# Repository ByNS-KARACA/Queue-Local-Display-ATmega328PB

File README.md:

# Queue Local Display – ATmega328PB

A modular local queue display controller designed for queue management systems used in hospitals, banks, clinics, public institutions, service counters, and similar environments.

The system is built around the **Microchip ATmega328PB** microcontroller and supports both wired **RS-485 communication** and optional **433 MHz HC-12 wireless communication**.

The display section uses cascaded **HEF4094BT shift registers**, allowing multiple large 7-segment displays to be controlled with only a few MCU pins.

## Features

* Microchip **ATmega328PB**
* 5 V MCU operation
* External **16 MHz crystal**
* 12 V DC input
* **AP63205WU-7** synchronous buck converter for 12 V to 5 V
* **MAX485** RS-485 interface
* Optional **HC-12 433 MHz wireless module**
* Independent hardware UARTs for RS-485 and HC-12
* **HEF4094BT** cascaded display architecture
* **ULN2003A** 5 V to 12 V logic interface
* Static-drive 7-segment display architecture
* 6 × large 56 mm 7-segment display positions
* 2 display positions support optional FJ11001AH alternative displays
* EEPROM-based device addressing
* SET / UP / DOWN configuration buttons
* PWM-capable global display brightness control
* External I²C expansion interface
* Additional GPIO expansion pins
* RS-485 daisy-chain capability
* Optional RS-485 termination
* Designed for continuous **24/7 operation**

## 3D Preview

### Top & Bottom Views

### Angled View

## Manufacturing Files

Ready-to-manufacture Gerber and drill files are provided for this PCB.

- 📁 [Browse Gerber Files](Hardware/Gerber)
- 📦 [Download Complete Gerber ZIP](Hardware/Gerber/Queue_Local_Display_Atmega328PB_GERBER.zip)
- 🛠️ [KiCad Source Files](Hardware/KiCad)
- 📋 [Bill of Materials (BOM)](Hardware/BOM/Queue_Local_Display_ATmega328PB_BOM.xlsx)
The Gerber package includes the copper, solder mask, silkscreen, solder paste, board outline, plated-hole and non-plated-hole drill files required for PCB fabrication.

### PCB Specifications

| Parameter | Specification |
| --- | --- |
| Layers | 2 |
| PCB Thickness | 1.6 mm |
| Material | FR-4 |
| Copper Thickness | 35 µm / 1 oz |
| Board Size | approximately 340.05 × 100.05 mm |

> **Note:** Always verify the Gerber files and manufacturing parameters with your PCB manufacturer before placing an order.

## Display Configuration

The board uses:

### Main Queue Number

* 4 × **SM412301N**
* 2.3 inch / approximately 56 mm
* Red
* Common Anode
### Optional Alternative Display

Two display positions also support:

- 2 × **FJ11001AH**
- Smaller red 7-segment display
- Optional alternative to SM412301N
- Not populated simultaneously with SM412301N at the same position
### Counter / Desk Number

* 2 × **FJ11001AH**
* Red 7-segment display

Example display format:

```text
+--------------------------------+
|                                |
|       A 1 4 5       0 3        |
|                                |
|       QUEUE        COUNTER      |
+--------------------------------+
```

## Display Driver Architecture

Each 7-segment digit is controlled by its own **HEF4094BT** shift register.

The shift registers are connected in cascade:

```text
ATmega328PB
     |
     | DATA
     v
 HEF4094 #1
     |
    QS2
     v
 HEF4094 #2
     |
    QS2
     v
 HEF4094 #3
     |
    QS2
     v
 HEF4094 #4
     |
    QS2
     v
 HEF4094 #5
     |
    QS2
     v
 HEF4094 #6
```

CLOCK, STROBE and OE lines are shared between all HEF4094 devices.

The HEF4094 devices operate from the **12 V rail**.

A **ULN2003A open-collector interface** with 12 V pull-up resistors is used between the 5 V ATmega328PB and the 12 V HEF4094 control inputs.

## HEF4094 Control Pins

| Function | ATmega328PB |
| -------- | ----------- |
| DATA     | D4          |
| OE       | D5          |
| CLOCK    | D6          |
| STROBE   | D7          |

The OE line is connected to a PWM-capable MCU output, allowing global display brightness control.

## RS-485 Interface

The board uses a **MAX485** half-duplex RS-485 transceiver.

| Function  | ATmega328PB |
| --------- | ----------- |
| RS-485 RX | PD0 / RXD0  |
| RS-485 TX | PD1 / TXD0  |
| RE + DE   | PB0 / D8    |

The RE and DE pins are connected together and controlled from a single GPIO.

The board is designed for **RS-485 bus / daisy-chain wiring**.

```text
MASTER
   |
LOCAL DISPLAY 01
   |
LOCAL DISPLAY 02
   |
LOCAL DISPLAY 03
   |
LOCAL DISPLAY 04
```

A termination resistor footprint is provided for installations where the display is located at the physical end of the RS-485 bus.

## HC-12 Wireless Interface

An optional **HC-12 433 MHz UART module** can be installed.

ATmega328PB USART1 is used for wireless communication.

| Function  | ATmega328PB |
| --------- | ----------- |
| HC-12 RX  | PB3 / TXD1  |
| HC-12 TX  | PB4 / RXD1  |
| HC-12 SET | PB2 / D10   |

The SET input includes a pull-up resistor to keep the HC-12 in normal operating mode during startup.

## Device Address Configuration

Each local display can be assigned an individual device address.

Three buttons are used:

* **SET**
* **UP**
* **DOWN**

The selected address is stored in the internal EEPROM of the ATmega328PB.

This eliminates the need for DIP switches and simplifies installation and field configuration.

## Power Architecture

```text
12 V DC INPUT
      |
      +--------------------> Displays / HEF4094 / LEDs
      |
      +----> AP63205WU-7
                  |
                  v
                 5 V
                  |
                  +----> ATmega328PB
                  +----> MAX485
                  +----> HC-12
```

The **AP63205WU-7** provides the regulated 5 V logic supply.

The 12 V rail directly supplies the display driver section and external indicators.

## Expansion

Unused ATmega328PB GPIO pins are exposed for future expansion.

Possible future uses include:

* Status LEDs
* Additional buttons
* External sensors
* Relay outputs
* ADC inputs
* Interrupt inputs
* Additional I²C devices
* External indicators

The primary external I²C interface is:

```text
PC4 → SDA0
PC5 → SCL0
```

## Applications

* Hospital queue systems
* Bank queue systems
* Clinic waiting-room displays
* Government service counters
* Pharmacy queue systems
* Restaurant queue systems
* Reception systems
* Service desk displays

## Modular Architecture

The hardware is designed with future modular expansion in mind.

Multiple local display boards can later be combined to create a multi-row **main queue display**, while maintaining a common hardware platform.

## Project Status

**Hardware Design:** Completed
**Firmware:** In Development
**Production Validation:** Pending

This project is currently in the prototype and validation stage.

## Disclaimer

This hardware should be fully tested and validated before use in commercial, medical, industrial, or safety-critical installations.

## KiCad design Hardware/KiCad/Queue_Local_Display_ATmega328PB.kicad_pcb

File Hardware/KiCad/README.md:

# KiCad Design Files

This directory contains the KiCad source files for the Queue Local Display hardware.

## Files

- Schematic design
- PCB layout
- KiCad project file

These files represent the editable hardware source of the project.

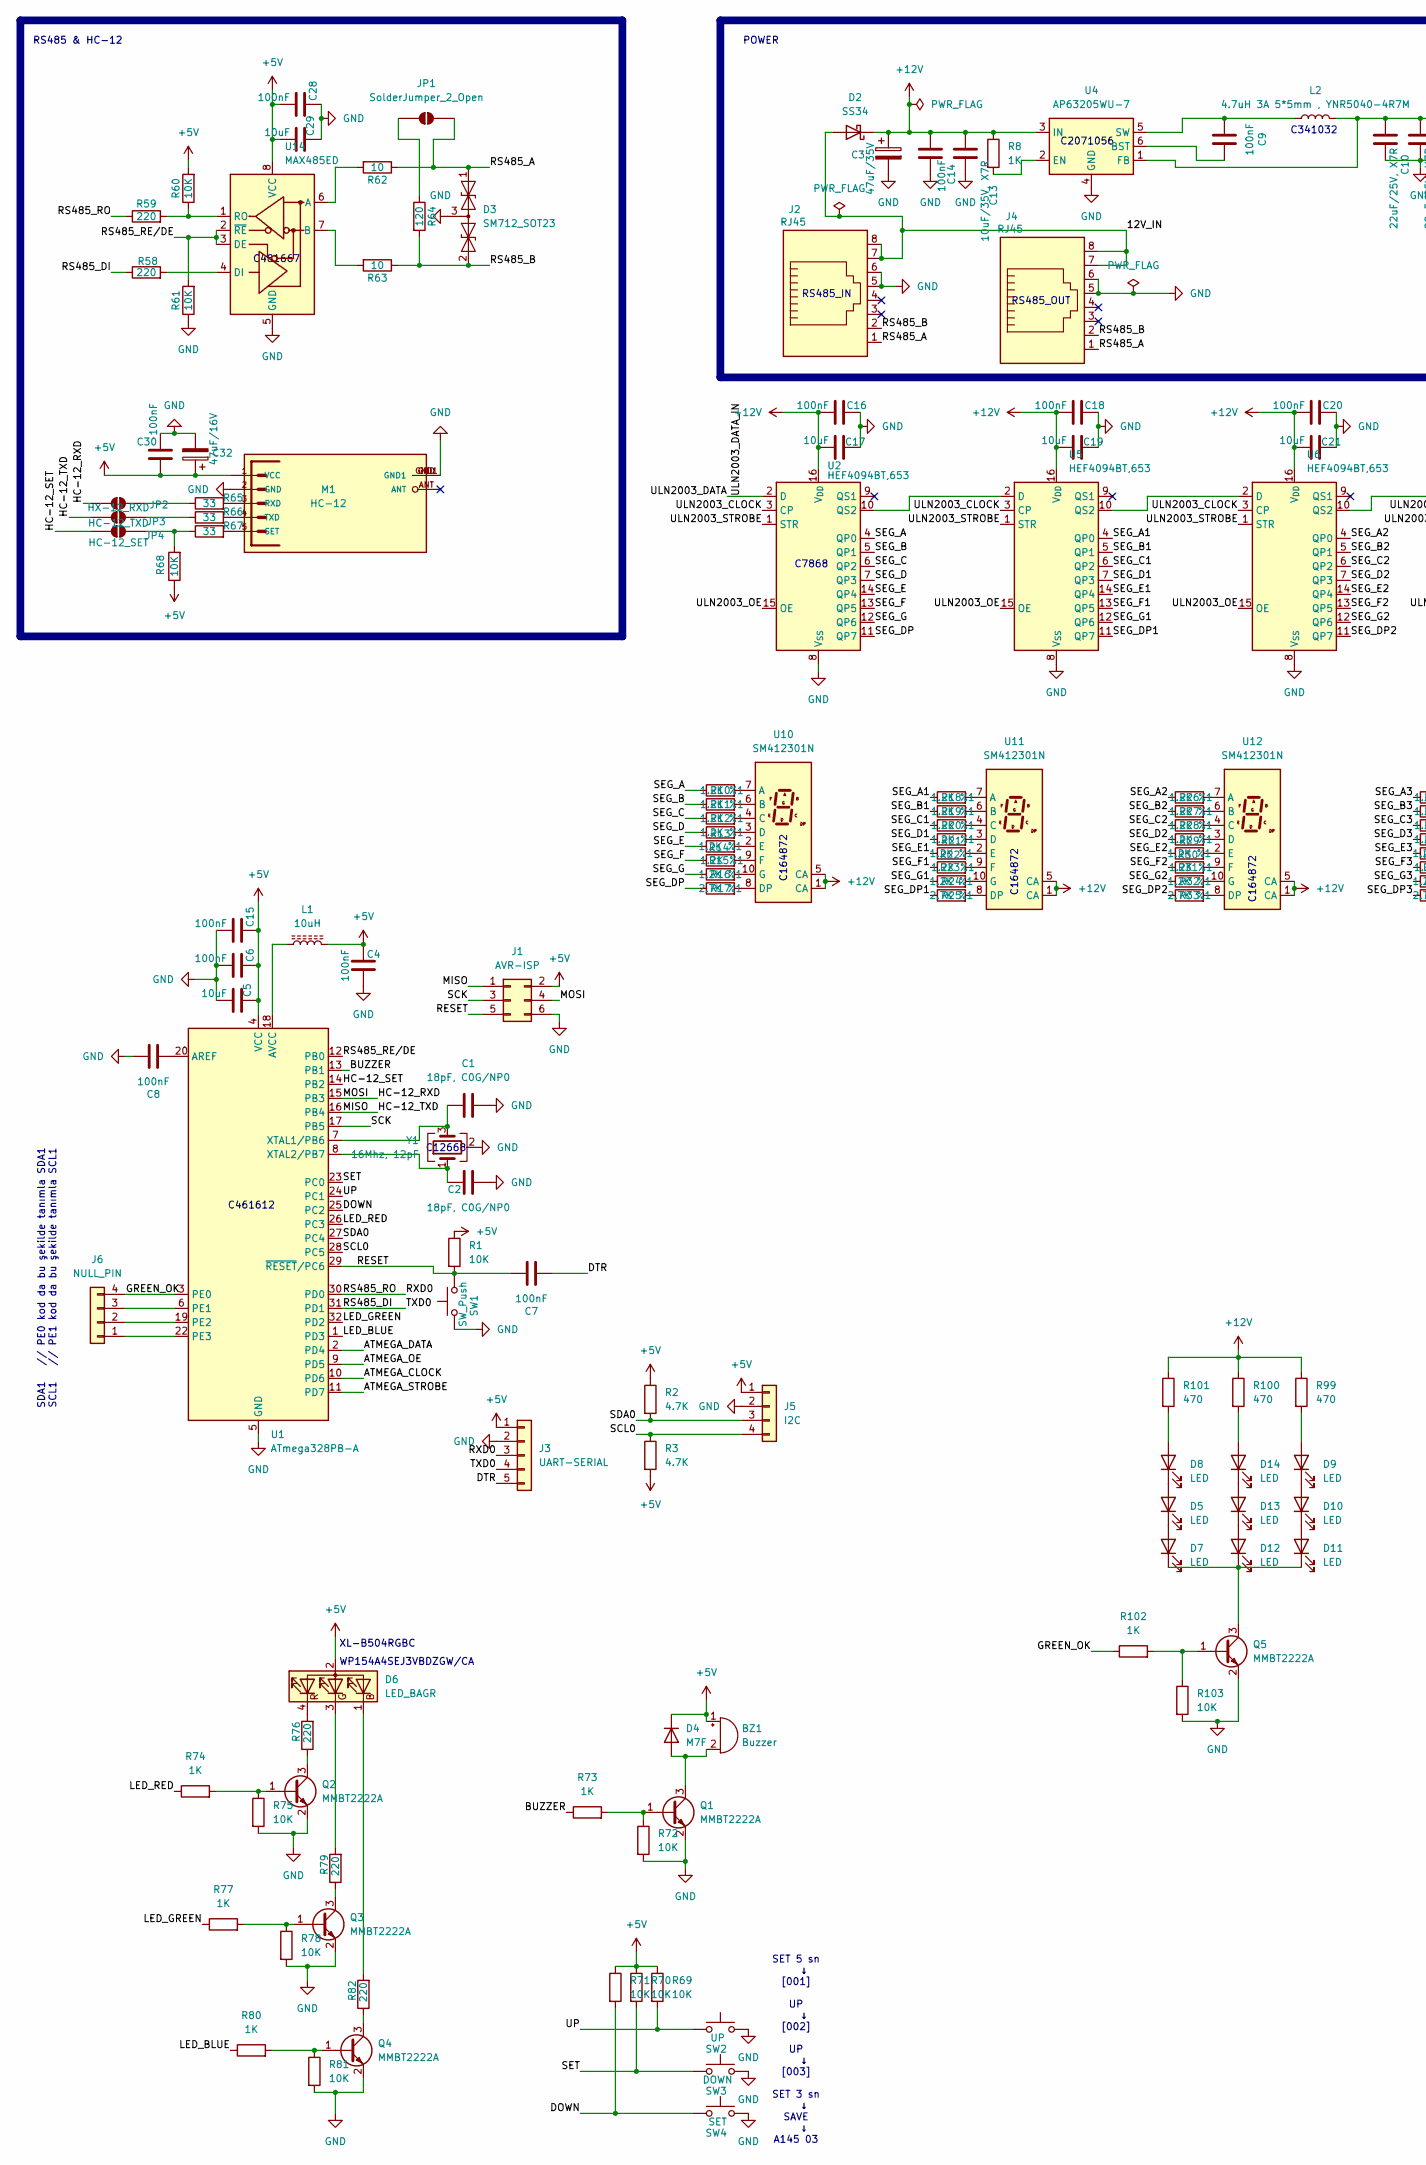
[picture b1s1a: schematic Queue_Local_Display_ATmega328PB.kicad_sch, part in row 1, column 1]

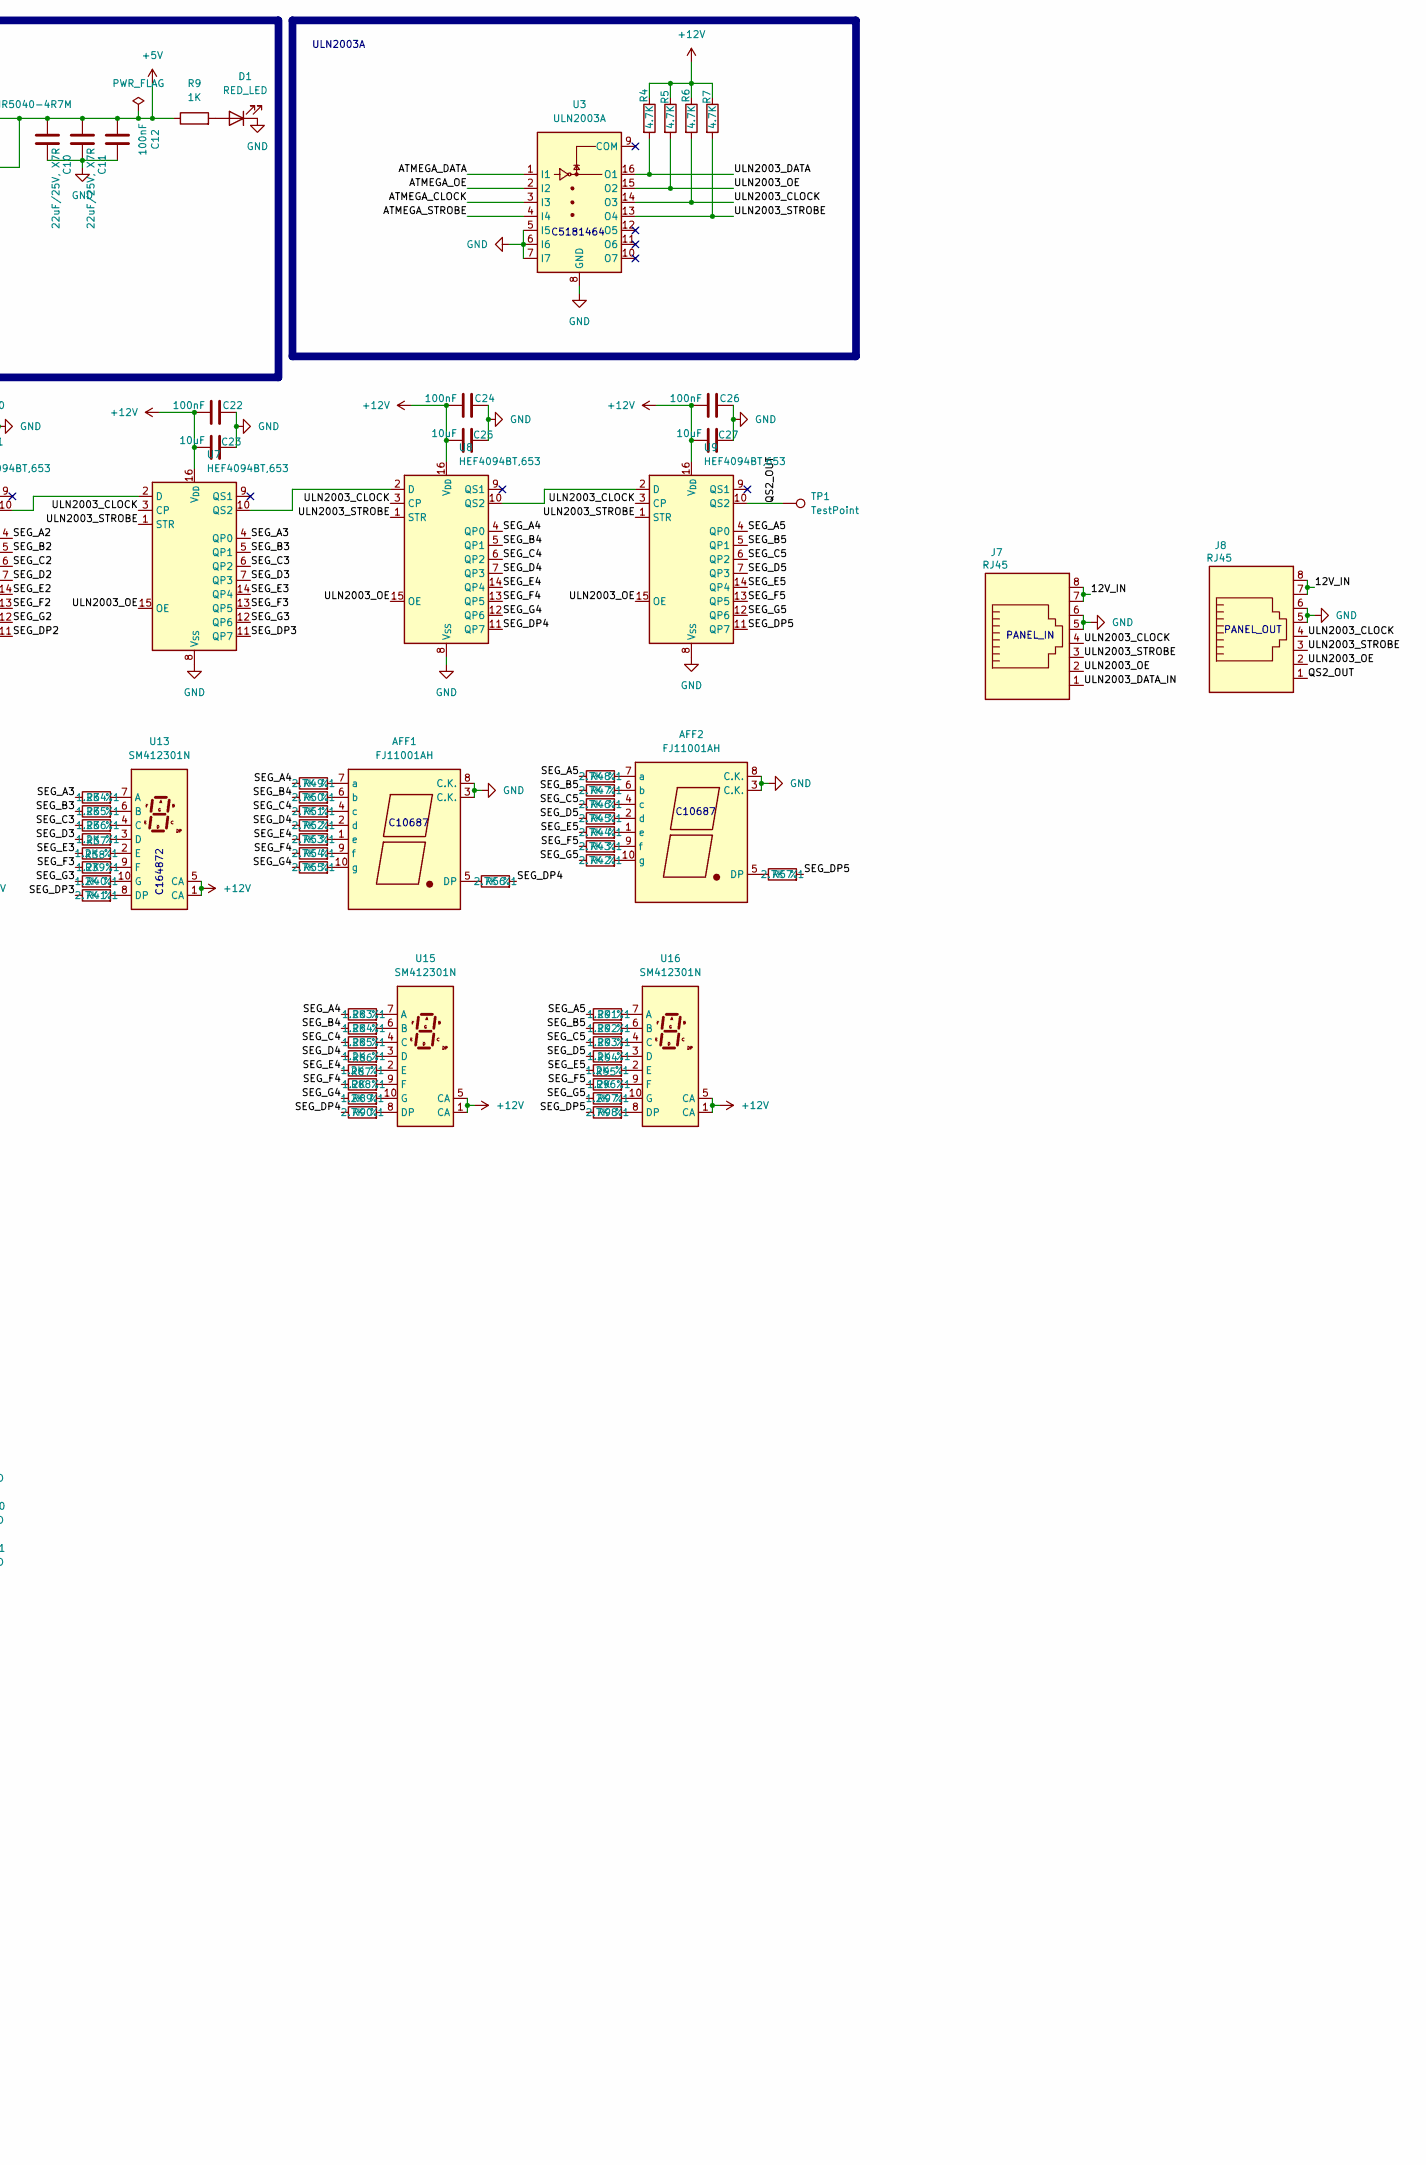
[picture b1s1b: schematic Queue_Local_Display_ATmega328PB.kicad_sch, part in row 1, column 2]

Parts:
AFF1, AFF2: FJ11001AH; 7SegmentLED_LTS6760_LTS6780
BZ1: Buzzer; Buzzer_12x9.5RM7.6
C1, C2: 18pF, C0G/NP0; C_0603_1608Metric
C3: 47uF/35V; CP_Elec_6.3x5.4
C4, C6, C8, C15, C16, C18, C20, C22, C24, C26, C28, C30: 100nF; C_0603_1608Metric
C5, C17, C19, C21, C23, C25, C27, C29: 10uF; C_0805_2012Metric
C7, C9, C12, C14: 100nF; C_0805_2012Metric
C10, C11: 22uF/25V, X7R; C_1206_3216Metric
C13: 10uF/35V, X7R; C_1206_3216Metric
C32: 47uF/16V; CP_Elec_5x5.7
D1: RED_LED; LED_0805_2012Metric
D2: SS34; D_SMA
D3: SM712_SOT23; SOT-23
D4: M7F; D_SMA
D5, D7, D8, D9, D10, D11, D12, D13, D14: LED; LED_1206_3216Metric
D6: LED_BAGR; LED_D5.0mm-4_RGB_Wide_Pins
J1: AVR-ISP; PinHeader_2x03_P2.54mm_Vertical
J2, J4, J7, J8: RJ45; RJ45_Amphenol_54602-x08_Horizontal
J3: UART-SERIAL; PinHeader_1x05_P2.54mm_Vertical
J5: I2C; PinHeader_1x04_P2.54mm_Vertical
J6: NULL_PIN; PinHeader_1x04_P2.54mm_Vertical
JP1: SolderJumper_2_Open; SolderJumper-2_P1.3mm_Open_RoundedPad1.0x1.5mm
JP2: HX-12_RXD; SolderJumper-2_P1.3mm_Open_RoundedPad1.0x1.5mm
JP3: HC-12_TXD; SolderJumper-2_P1.3mm_Open_RoundedPad1.0x1.5mm
JP4: HC-12_SET; SolderJumper-2_P1.3mm_Open_RoundedPad1.0x1.5mm
L1: 10uH; L_0603_1608Metric
L2: 4.7uH 3A 5*5mm , YNR5040-4R7M; L_Chilisin_BWVS00505040
M1: HC-12; MA05-1
Q1, Q2, Q3, Q4, Q5: MMBT2222A; SOT-23
R1, R60, R61, R68: 10K; R_0805_2012Metric
R2, R3, R4, R5, R6, R7: 4.7K; R_0805_2012Metric
R8, R9: 1K; R_0805_2012Metric
R10, R11, R12, R13, R14, R15, R16, R18, R19, R20, R21, R22, R23, R24, R26, R27, R28, R29, R30, R31, R32, R34, R35, R36, R37, R38, R39, R40, R83, R84, R85, R86, R87, R88, R89, R91, R92, R93, R94, R95, R96, R97: 1.2K %1; R_0805_2012Metric
R17, R25, R33, R41, R42, R43, R44, R45, R46, R47, R48, R49, R50, R51, R52, R53, R54, R55, R56, R57, R90, R98: 2.7K %1; R_0805_2012Metric
R58, R59: 220; R_0805_2012Metric
R62, R63: 10; R_0805_2012Metric
R64: 120; R_0805_2012Metric
R65, R66, R67: 33; R_0805_2012Metric
R69, R70, R71, R72, R75, R78, R81, R103: 10K; R_0603_1608Metric
R73, R74, R77, R80, R102: 1K; R_0603_1608Metric
R76, R79, R82: 220; R_0603_1608Metric
R99, R100, R101: 470; R_0805_2012Metric
SW1: SW_Push; SW_PUSH_6mm_H13mm
SW2: UP; SW_PUSH_6mm_H13mm
SW3: DOWN; SW_PUSH_6mm_H13mm
SW4: SET; SW_PUSH_6mm_H13mm
TP1: TestPoint; TestPoint_Pad_2.0x2.0mm
U1: ATmega328PB-A; TQFP-32_7x7mm_P0.8mm
U2, U5, U6, U7, U8, U9: HEF4094BT,653; SOIC-16_3.9x9.9mm_P1.27mm
U3: ULN2003A; SOIC-16_3.9x9.9mm_P1.27mm
U4: AP63205WU-7; TSOT-23-6
U10, U11, U12, U13, U15, U16: SM412301N; SA15-11xxx
U14: MAX485ED; SOIC-8_3.9x4.9mm_P1.27mm
Y1: 16Mhz, 12pF; Crystal_SMD_3225-4Pin_3.2x2.5mm

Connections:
+5V: BZ1.1 (+), C4.1, C5.2, C6.2, C10.1, C11.1, C12.1, C15.2, C28.1, C29.1, C30.1, C32.1, D4.1 (K), D6.2 (A), J1.2, J3.1, J5.1, L1.2, L2.2, M1.1 (VCC), R1.1, R2.1, R3.2, R9.1, R60.2, R68.1, R69.1, R70.1, R71.1, U1.4 (VCC), U4.1 (FB), U14.8 (VCC)
+12V: C3.1, C13.1, C14.1, C16.1, C17.1, C18.1, C19.1, C20.1, C21.1, C22.1, C23.1, C24.1, C25.1, C26.1, C27.1, D2.1 (K), R4.1, R5.1, R6.1, R7.1, R8.1, R99.1, R100.1, R101.1, U2.16 (V_{DD}), U4.3 (IN), U5.16 (V_{DD}), U6.16 (V_{DD}), U7.16 (V_{DD}), U8.16 (V_{DD}), U9.16 (V_{DD}), U10.1 (CA), U10.5 (CA), U11.1 (CA), U11.5 (CA), U12.1 (CA), U12.5 (CA), U13.1 (CA), U13.5 (CA), U15.1 (CA), U15.5 (CA), U16.1 (CA), U16.5 (CA)
/12V_IN: D2.2 (A), J2.7, J2.8, J4.7, J4.8, J7.7, J7.8, J8.7, J8.8
/ATMEGA_CLOCK: U1.10 (PD6), U3.3 (I3)
/ATMEGA_DATA: U1.2 (PD4), U3.1 (I1)
/ATMEGA_OE: U1.9 (PD5), U3.2 (I2)
/ATMEGA_STROBE: U1.11 (PD7), U3.4 (I4)
/BUZZER: R73.1, U1.13 (PB1)
/DTR: C7.1, J3.5
/GREEN_OK: J6.4, R102.1, U1.3 (PE0)
/HC-12_RXD: J1.4, JP2.1 (A), U1.15 (PB3)
/HC-12_SET: JP4.1 (A), U1.14 (PB2)
/HC-12_TXD: J1.1, JP3.1 (A), U1.16 (PB4)
/LED_BLUE: R80.1, U1.1 (PD3)
/LED_GREEN: R77.1, U1.32 (PD2)
/LED_RED: R74.1, U1.26 (PC3)
/QS2_OUT: J8.1, TP1.1 (1_1), U9.10 (QS2)
/RESET: C7.2, J1.5, R1.2, SW1.2, U1.29 (~RESET/PC6)
/RS485_A: D3.1 (A1), J2.1, J4.1, JP1.2 (B), R62.1
/RS485_B: D3.2 (A2), J2.2, J4.2, R63.1, R64.2
/RS485_DI: J3.4, R58.1, U1.31 (PD1)
/RS485_RE/DE: R61.2, U1.12 (PB0), U14.2 (~RE), U14.3 (DE)
/RS485_RO: J3.3, R59.1, U1.30 (PD0)
/SCK: J1.3, U1.17 (PB5)
/SCL0: J5.4, R3.1, U1.28 (PC5)
/SDA0: J5.3, R2.2, U1.27 (PC4)
/SEG_A: R10.1, U2.4 (QP0)
/SEG_A1: R18.1, U5.4 (QP0)
/SEG_A2: R26.1, U6.4 (QP0)
/SEG_A3: R34.1, U7.4 (QP0)
/SEG_A4: R49.1, R83.1, U8.4 (QP0)
/SEG_A5: R48.1, R91.1, U9.4 (QP0)
/SEG_B: R11.1, U2.5 (QP1)
/SEG_B1: R19.1, U5.5 (QP1)
/SEG_B2: R27.1, U6.5 (QP1)
/SEG_B3: R35.1, U7.5 (QP1)
/SEG_B4: R50.1, R84.1, U8.5 (QP1)
/SEG_B5: R47.1, R92.1, U9.5 (QP1)
/SEG_C: R12.1, U2.6 (QP2)
/SEG_C1: R20.1, U5.6 (QP2)
/SEG_C2: R28.1, U6.6 (QP2)
/SEG_C3: R36.1, U7.6 (QP2)
/SEG_C4: R51.1, R85.1, U8.6 (QP2)
/SEG_C5: R46.1, R93.1, U9.6 (QP2)
/SEG_D: R13.1, U2.7 (QP3)
/SEG_D1: R21.1, U5.7 (QP3)
/SEG_D2: R29.1, U6.7 (QP3)
/SEG_D3: R37.1, U7.7 (QP3)
/SEG_D4: R52.1, R86.1, U8.7 (QP3)
/SEG_D5: R45.1, R94.1, U9.7 (QP3)
/SEG_DP: R17.1, U2.11 (QP7)
/SEG_DP1: R25.1, U5.11 (QP7)
/SEG_DP2: R33.1, U6.11 (QP7)
/SEG_DP3: R41.1, U7.11 (QP7)
/SEG_DP4: R56.2, R90.1, U8.11 (QP7)
/SEG_DP5: R57.2, R98.1, U9.11 (QP7)
/SEG_E: R14.1, U2.14 (QP4)
/SEG_E1: R22.1, U5.14 (QP4)
/SEG_E2: R30.1, U6.14 (QP4)
/SEG_E3: R38.1, U7.14 (QP4)
/SEG_E4: R53.1, R87.1, U8.14 (QP4)
/SEG_E5: R44.1, R95.1, U9.14 (QP4)
/SEG_F: R15.1, U2.13 (QP5)
/SEG_F1: R23.1, U5.13 (QP5)
/SEG_F2: R31.1, U6.13 (QP5)
/SEG_F3: R39.1, U7.13 (QP5)
/SEG_F4: R54.1, R88.1, U8.13 (QP5)
/SEG_F5: R43.1, R96.1, U9.13 (QP5)
/SEG_G: R16.1, U2.12 (QP6)
/SEG_G1: R24.1, U5.12 (QP6)
/SEG_G2: R32.1, U6.12 (QP6)
/SEG_G3: R40.1, U7.12 (QP6)
/SEG_G4: R55.1, R89.1, U8.12 (QP6)
/SEG_G5: R42.1, R97.1, U9.12 (QP6)
/ULN2003_CLOCK: J7.4, J8.4, R6.2, U2.3 (CP), U3.14 (O3), U5.3 (CP), U6.3 (CP), U7.3 (CP), U8.3 (CP), U9.3 (CP)
/ULN2003_DATA: J7.1, R4.2, U2.2 (D), U3.16 (O1)
/ULN2003_OE: J7.2, J8.2, R5.2, U2.15 (OE), U3.15 (O2), U5.15 (OE), U6.15 (OE), U7.15 (OE), U8.15 (OE), U9.15 (OE)
/ULN2003_STROBE: J7.3, J8.3, R7.2, U2.1 (STR), U3.13 (O4), U5.1 (STR), U6.1 (STR), U7.1 (STR), U8.1 (STR), U9.1 (STR)
/UP: R69.2, SW2.1, U1.24 (PC1)
GND: AFF1.3 (C.K.), AFF1.8 (C.K.), AFF2.3 (C.K.), AFF2.8 (C.K.), C1.2, C2.1, C3.2, C4.2, C5.1, C6.1, C8.2, C10.2, C11.2, C12.2, C13.2, C14.2, C15.1, C16.2, C17.2, C18.2, C19.2, C20.2, C21.2, C22.2, C23.2, C24.2, C25.2, C26.2, C27.2, C28.2, C29.2, C30.2, C32.2, D1.1 (K), D3.3 (common), J1.6, J2.5, J2.6, J3.2, J4.5, J4.6, J5.2, J7.5, J7.6, J8.5, J8.6, M1.2 (GND), M1.GND (GND1), M1.GND1, Q1.2 (E), Q2.2 (E), Q3.2 (E), Q4.2 (E), Q5.2 (E), R61.1, R72.2, R75.2, R78.2, R81.2, R103.2, SW1.1, SW2.2, SW3.2, SW4.2, U1.5 (GND), U1.21 (GND), U2.8 (V_{SS}), U3.5 (I5), U3.6 (I6), U3.7 (I7), U3.8 (GND), U4.4 (GND), U5.8 (V_{SS}), U6.8 (V_{SS}), U7.8 (V_{SS}), U8.8 (V_{SS}), U9.8 (V_{SS}), U14.5 (GND), Y1.2 (G), Y1.4 (G)
unnamed: AFF1.5 (DP), R56.1
unnamed: AFF1.7 (a), R49.2
unnamed: AFF1.6 (b), R50.2
unnamed: AFF1.4 (c), R51.2
unnamed: AFF1.2 (d), R52.2
unnamed: AFF1.1 (e), R53.2
unnamed: AFF1.9 (f), R54.2
unnamed: AFF1.10 (g), R55.2
unnamed: AFF2.5 (DP), R57.1
unnamed: AFF2.7 (a), R48.2
unnamed: AFF2.6 (b), R47.2
unnamed: AFF2.4 (c), R46.2
unnamed: AFF2.2 (d), R45.2
unnamed: AFF2.1 (e), R44.2
unnamed: AFF2.9 (f), R43.2
unnamed: AFF2.10 (g), R42.2
unnamed: BZ1.2 (-), D4.2 (A), Q1.3 (C)
unnamed: D1.2 (A), R9.2
unnamed: D5.2 (A), D8.1 (K)
unnamed: D5.1 (K), D7.2 (A)
unnamed: D6.1 (BK), R82.2
unnamed: D6.3 (GK), R79.2
unnamed: D6.4 (RK), R76.2
unnamed: D8.2 (A), R101.2
unnamed: D9.2 (A), R99.2
unnamed: D9.1 (K), D10.2 (A)
unnamed: D10.1 (K), D11.2 (A)
unnamed: D7.1 (K), D11.1 (K), D12.1 (K), Q5.3 (C)
unnamed: D12.2 (A), D13.1 (K)
unnamed: D13.2 (A), D14.1 (K)
unnamed: D14.2 (A), R100.2
unnamed: J6.1, U1.22 (PE3)
unnamed: J6.2, U1.19 (PE2)
unnamed: J6.3, U1.6 (PE1)
unnamed: JP1.1 (A), R64.1
unnamed: JP2.2 (B), R65.1
unnamed: JP3.2 (B), R66.1
unnamed: JP4.2 (B), R67.1, R68.2
unnamed: M1.3 (RXD), R65.2
unnamed: M1.5 (SET), R67.2
unnamed: M1.4 (TXD), R66.2
unnamed: Q1.1 (B), R72.1, R73.2
unnamed: Q2.1 (B), R74.2, R75.1
unnamed: Q2.3 (C), R76.1
unnamed: Q3.1 (B), R77.2, R78.1
unnamed: Q3.3 (C), R79.1
unnamed: Q4.1 (B), R80.2, R81.1
unnamed: Q4.3 (C), R82.1
unnamed: Q5.1 (B), R102.2, R103.1
unnamed: C8.1, U1.20 (AREF)
unnamed: L1.1, U1.18 (AVCC)
unnamed: C1.1, U1.7 (XTAL1/PB6), Y1.3
unnamed: C2.2, U1.8 (XTAL2/PB7), Y1.1
unnamed: U2.10 (QS2), U5.2 (D)
unnamed: C9.2, U4.6 (BST)
unnamed: R8.2, U4.2 (EN)
unnamed: C9.1, L2.1, U4.5 (SW)
unnamed: U5.10 (QS2), U6.2 (D)
unnamed: U6.10 (QS2), U7.2 (D)
unnamed: U7.10 (QS2), U8.2 (D)
unnamed: U8.10 (QS2), U9.2 (D)
unnamed: R10.2, U10.7 (A)
unnamed: R11.2, U10.6 (B)
unnamed: R12.2, U10.4 (C)
unnamed: R13.2, U10.3 (D)
unnamed: R17.2, U10.8 (DP)
unnamed: R14.2, U10.2 (E)
unnamed: R15.2, U10.9 (F)
unnamed: R16.2, U10.10 (G)
unnamed: R18.2, U11.7 (A)
unnamed: R19.2, U11.6 (B)
unnamed: R20.2, U11.4 (C)
unnamed: R21.2, U11.3 (D)
unnamed: R25.2, U11.8 (DP)
unnamed: R22.2, U11.2 (E)
unnamed: R23.2, U11.9 (F)
unnamed: R24.2, U11.10 (G)
unnamed: R26.2, U12.7 (A)
unnamed: R27.2, U12.6 (B)
unnamed: R28.2, U12.4 (C)
unnamed: R29.2, U12.3 (D)
unnamed: R33.2, U12.8 (DP)
unnamed: R30.2, U12.2 (E)
unnamed: R31.2, U12.9 (F)
unnamed: R32.2, U12.10 (G)
unnamed: R34.2, U13.7 (A)
unnamed: R35.2, U13.6 (B)
unnamed: R36.2, U13.4 (C)
unnamed: R37.2, U13.3 (D)
unnamed: R41.2, U13.8 (DP)
unnamed: R38.2, U13.2 (E)
unnamed: R39.2, U13.9 (F)
unnamed: R40.2, U13.10 (G)
unnamed: R62.2, U14.6 (A)
unnamed: R63.2, U14.7 (B)
unnamed: R58.2, U14.4 (DI)
unnamed: R59.2, R60.1, U14.1 (RO)
unnamed: R83.2, U15.7 (A)
unnamed: R84.2, U15.6 (B)
unnamed: R85.2, U15.4 (C)
unnamed: R86.2, U15.3 (D)
unnamed: R90.2, U15.8 (DP)
unnamed: R87.2, U15.2 (E)
unnamed: R88.2, U15.9 (F)
unnamed: R89.2, U15.10 (G)
unnamed: R91.2, U16.7 (A)
unnamed: R92.2, U16.6 (B)
unnamed: R93.2, U16.4 (C)
unnamed: R94.2, U16.3 (D)
unnamed: R98.2, U16.8 (DP)
unnamed: R95.2, U16.2 (E)
unnamed: R96.2, U16.9 (F)
unnamed: R97.2, U16.10 (G)

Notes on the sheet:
XL-B504RGBC
ULN2003A
C341032
RS485_IN
C164872
RS485 & HC-12
C5181464
C481667
C461612
SET 5 sn ↓ [001] UP ↓ [002] UP ↓ [003] SET 3 sn ↓ SAVE ↓ A145 03
C12668
RS485_OUT
POWER
C10687
SDA1 // PE0 kod da bu şekilde tanımla SDA1 SCL1 // PE1 kod da bu şekilde tanımla SCL1
C7868
PANEL_OUT
C2071056
PANEL_IN
WP154A4SEJ3VBDZGW/CA

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
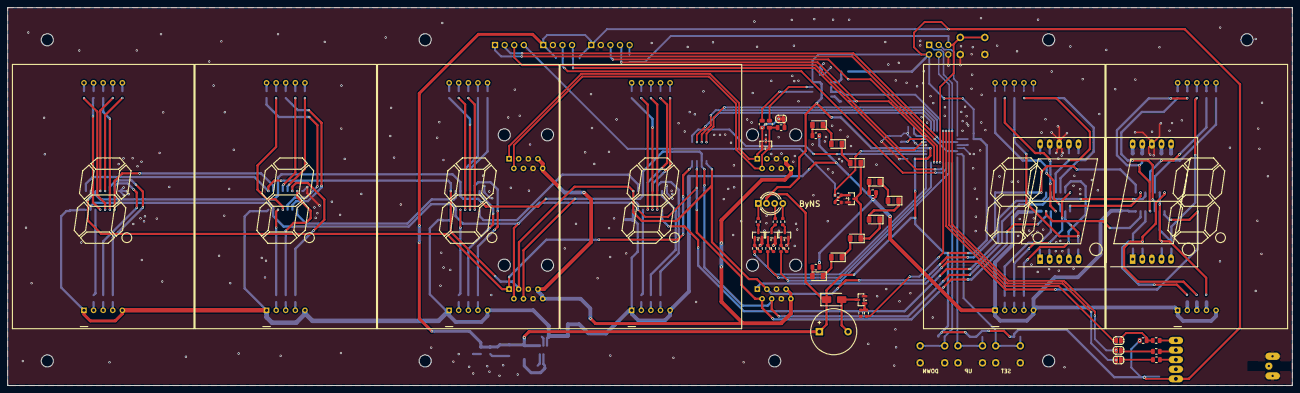
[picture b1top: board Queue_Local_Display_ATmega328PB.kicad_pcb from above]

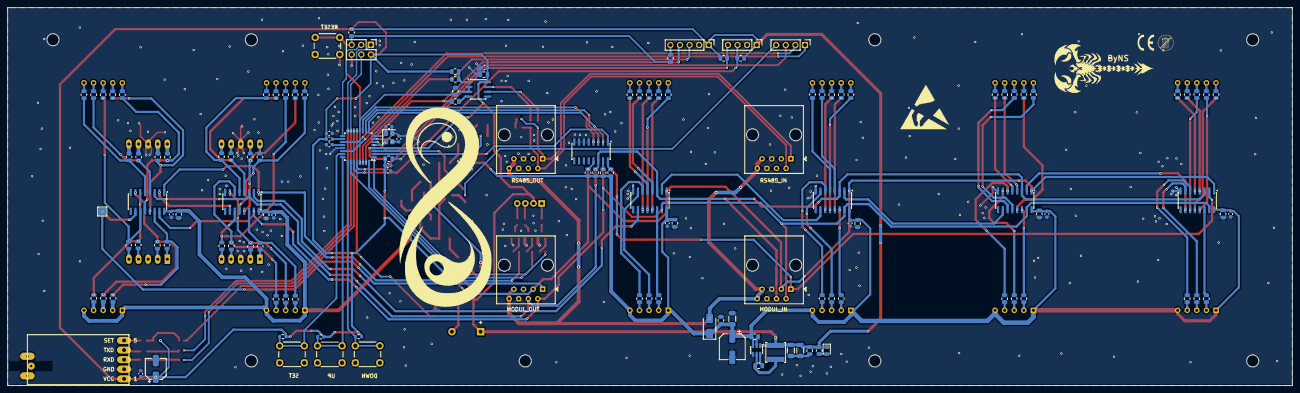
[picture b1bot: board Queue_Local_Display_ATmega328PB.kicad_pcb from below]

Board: 2 copper layers, 340.0 x 100.0 mm, 193 parts (140 on the bottom side), 195 nets.

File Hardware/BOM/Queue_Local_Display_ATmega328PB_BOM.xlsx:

| Sourced | Placed | References | Value | Footprint | Quantity | Notes
1 |  |  | C4, C6, C8, C15, C16, C18, C20, C22, C24, C26, C28, C30 | 100nF | C_0603_1608Metric | 12
2 |  |  | C5, C17, C19, C21, C23, C25, C27, C29 | 10uF | C_0805_2012Metric | 8
3 |  |  | C7, C9, C12, C14 | 100nF | C_0805_2012Metric | 4
4 |  |  | C1, C2 | 18pF, C0G/NP0 | C_0603_1608Metric | 2
5 |  |  | C10, C11 | 22uF/25V, X7R | C_1206_3216Metric | 2
6 |  |  | C3 | 47uF/35V | CP_Elec_6.3x5.4 | 1
7 |  |  | C13 | 10uF/35V, X7R | C_1206_3216Metric | 1
8 |  |  | C32 | 47uF/16V | CP_Elec_5x5.7 | 1
9 |  |  | R10, R11, R12, R13, R14, R15, R16, R18, R19, R20, R21, R22, R23, R24, R26, R27,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 | 1.2K %1 | R_0805_2012Metric | 42
10 |  |  | R17, R25, R33, R41, R42, R43, R44, R45, R46, R47, R48, R49, R50, R51, R52, R53,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 | 2.7K %1 | R_0805_2012Metric | 22
11 |  |  | R69, R70, R71, R72, R75, R78, R81, R103 | 10K | R_0603_1608Metric | 8
12 |  |  | R2, R3, R4, R5, R6, R7 | 4.7K | R_0805_2012Metric | 6
13 |  |  | R73, R74, R77, R80, R102 | 1K | R_0603_1608Metric | 5
14 |  |  | R1, R60, R61, R68 | 10K | R_0805_2012Metric | 4
15 |  |  | R65, R66, R67 | 33 | R_0805_2012Metric | 3
16 |  |  | R76, R79, R82 | 220 | R_0603_1608Metric | 3
17 |  |  | R99, R100, R101 | 470 | R_0805_2012Metric | 3
18 |  |  | R8, R9 | 1K | R_0805_2012Metric | 2
19 |  |  | R58, R59 | 220 | R_0805_2012Metric | 2
20 |  |  | R62, R63 | 10 | R_0805_2012Metric | 2
21 |  |  | R64 | 120 | R_0805_2012Metric | 1
22 |  |  | L1 | 10uH | L_0603_1608Metric | 1
23 | C341032 |  | L2 | 4.7uH 3A 5*5mm , YNR5040-4R7M | L_Chilisin_BWVS00505040 | 1
24 |  | GREEN_LED | D5, D7, D8, D9, D10, D11, D12, D13, D14 | GREEN_LED | LED_1206_3216Metric | 9
25 |  |  | D1 | RED_LED | LED_0805_2012Metric | 1
26 |  |  | D2 | SS34 | D_SMA | 1
27 |  |  | D3 | SM712_SOT23 | SOT-23 | 1
28 |  |  | D4 | M7F | D_SMA | 1
29 | XL-B504RGBC | CA_RGB_LED | D6 | LED_BAGR | LED_D5.0mm-4_RGB_Wide_Pins | 1
30 | C7868 |  | U2, U5, U6, U7, U8, U9 | HEF4094BT,653 | SOIC-16_3.9x9.9mm_P1.27mm | 6
31 | C164872 |  | U10, U11, U12, U13, U15, U16 | SM412301N | SA15-11xxx | 6 | Default display option. Six SM412301N displays are listed. Two of these display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
32 | C461612 | ATMEGA328PB | U1 | ATmega328PB-A | TQFP-32_7x7mm_P0.8mm | 1
33 | C5181464 |  | U3 | ULN2003A | SOIC-16_3.9x9.9mm_P1.27mm | 1
34 |  |  | U4 | AP63205WU-7 | TSOT-23-6 | 1
35 |  |  | U14 | MAX485ED | SOIC-8_3.9x4.9mm_P1.27mm | 1
36 | C12668 |  | Y1 | 16Mhz, 12pF | Crystal_SMD_3225-4Pin_3.2x2.5mm | 1
37 |  |  | SW1 | SW_Push | SW_PUSH_6mm_H13mm | 1
38 |  |  | SW2 | UP | SW_PUSH_6mm_H13mm | 1
39 |  |  | SW3 | DOWN | SW_PUSH_6mm_H13mm | 1
40 |  |  | SW4 | SET | SW_PUSH_6mm_H13mm | 1
41 |  |  | Q1, Q2, Q3, Q4, Q5 | MMBT2222A | SOT-23 | 5
42 | C10687 |  | AFF1, AFF2 | FJ11001AH | 7SegmentLED_LTS6760_LTS6780 | 2 | OPTIONAL ALTERNATIVE / DNP by default. FJ11001AH can replace two SM412301N disp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
43 |  |  | BZ1 | Buzzer | Buzzer_12x9.5RM7.6 | 1
44 |  |  | M1 | HC-12 | MA05-1 | 1
45 |  |  | TP1 | TestPoint | TestPoint_Pad_2.0x2.0mm | 1
46 |  |  | J2, J4, J7, J8 | RJ45 | RJ45_Amphenol_54602-x08_Horizontal | 4
47 |  |  | J1 | AVR-ISP | PinHeader_2x03_P2.54mm_Vertical | 1
48 |  |  | J3 | UART-SERIAL | PinHeader_1x05_P2.54mm_Vertical | 1
49 |  |  | J5 | I2C | PinHeader_1x04_P2.54mm_Vertical | 1
50 |  |  | J6 | NULL_PIN | PinHeader_1x04_P2.54mm_Vertical | 1
 |  | NOTE-1 | Orange-colored companents will be supplied but will not be mounted on the board.
 |  | NOTE-2 | Red-colored companents will not be supplied and will not be mounted on the boar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
 |  | NOTE-3 | **COMPONENT SELECTION NOTE** The manufacturer part numbers listed in this BOM a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
 |  | NOTE-4 | **DISPLAY OPTION NOTE** The standard configuration uses 6 × SM412301N displays.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
